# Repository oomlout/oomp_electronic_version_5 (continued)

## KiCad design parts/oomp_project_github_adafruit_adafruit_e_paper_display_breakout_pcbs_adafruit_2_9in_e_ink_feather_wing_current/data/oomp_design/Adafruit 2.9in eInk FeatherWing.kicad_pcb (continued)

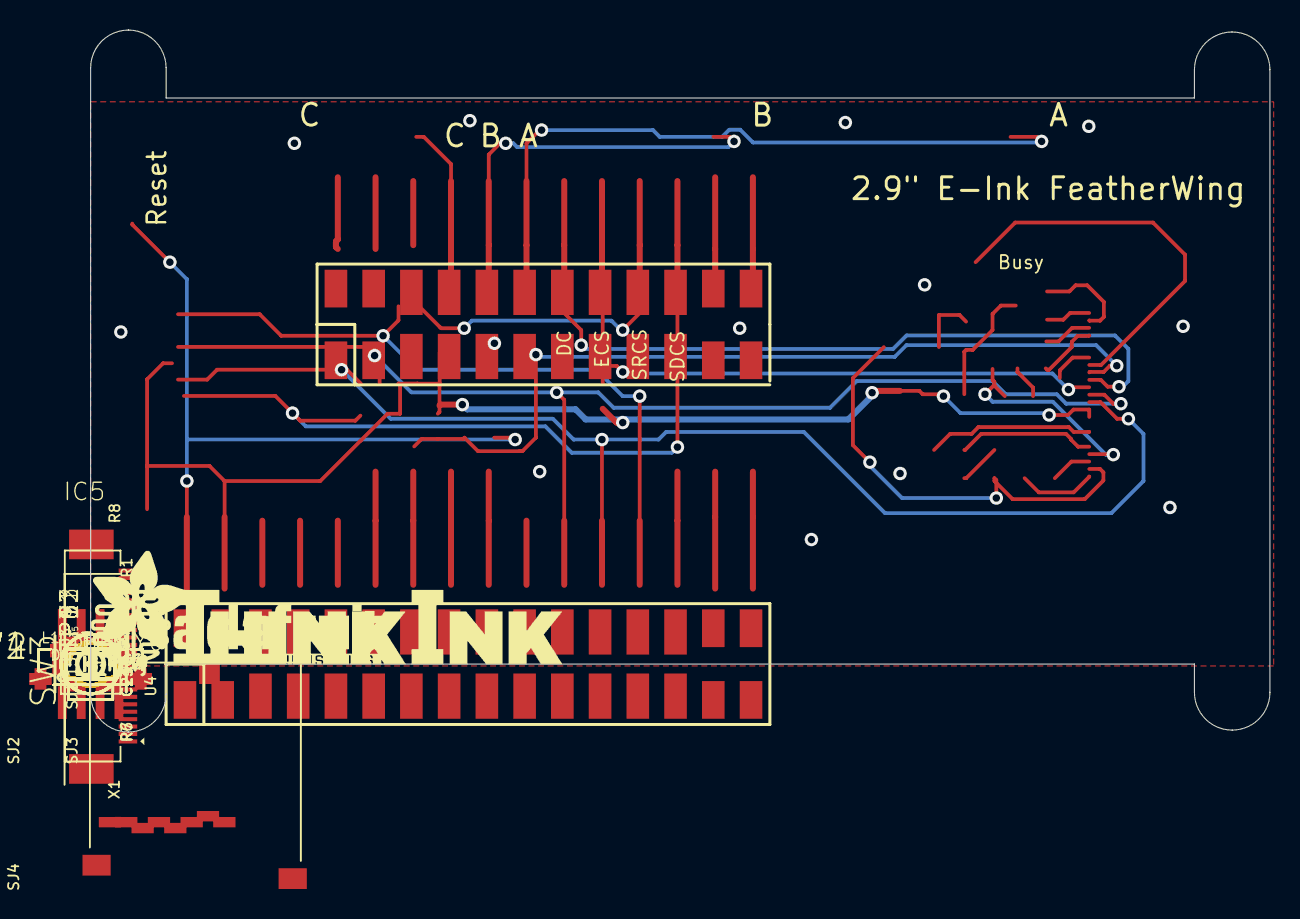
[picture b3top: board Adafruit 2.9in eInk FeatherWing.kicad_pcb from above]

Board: 2 copper layers, 79.4 x 47.2 mm, 59 parts (1 on the bottom side), 46 nets.

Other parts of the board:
U$8: THINKINK_1.25IN
U$9: PCBFEAT-REV-040
U$17: ADAFRUIT_TEXT_20MM

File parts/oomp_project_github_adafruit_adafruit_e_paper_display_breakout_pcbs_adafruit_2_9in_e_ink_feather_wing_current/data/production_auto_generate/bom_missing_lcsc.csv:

Designator,Comment,Footprint,OOMP ID,Reason
BUSY0,TPTP15SQ,Adafruit 2.9in eInk FeatherWing-import-fps:TP15SQ,,No verified LCSC part number
C1,1uF,Adafruit 2.9in eInk FeatherWing-import-fps:0805_10MGAP,,No verified LCSC part number
C2,1uF/10V,Adafruit 2.9in eInk FeatherWing-import-fps:0805-NO,,No verified LCSC part number
C3,1uF/25V,Adafruit 2.9in eInk FeatherWing-import-fps:0805-NO,,No verified LCSC part number
C4,1uF/25V,Adafruit 2.9in eInk FeatherWing-import-fps:0805-NO,,No verified LCSC part number
C5,10uF/25V,Adafruit 2.9in eInk FeatherWing-import-fps:0805-NO,electronic_capacitor_0805_10_micro_farad,No verified LCSC part number
C6,1uF/10V,Adafruit 2.9in eInk FeatherWing-import-fps:0805-NO,,No verified LCSC part number
C15,10uF/10V+,Adafruit 2.9in eInk FeatherWing-import-fps:0805-NO,electronic_capacitor_0805_10_micro_farad,No verified LCSC part number
C16,1uF,Adafruit 2.9in eInk FeatherWing-import-fps:0805-NO,,No verified LCSC part number
C21,10µF,Adafruit 2.9in eInk FeatherWing-import-fps:0805-NO,electronic_capacitor_0805_10_micro_farad,No verified LCSC part number
C22,1uF/25V,Adafruit 2.9in eInk FeatherWing-import-fps:0805-NO,,No verified LCSC part number
C23,1uF/25V,Adafruit 2.9in eInk FeatherWing-import-fps:0805-NO,,No verified LCSC part number
C24,1uF,Adafruit 2.9in eInk FeatherWing-import-fps:0805-NO,,No verified LCSC part number
D1,MBR0530,Adafruit 2.9in eInk FeatherWing-import-fps:SOD-123,,No verified LCSC part number
D2,MBR0530,Adafruit 2.9in eInk FeatherWing-import-fps:SOD-123,,No verified LCSC part number
D3,MBR0530,Adafruit 2.9in eInk FeatherWing-import-fps:SOD-123,,No verified LCSC part number
D4,1N4148,Adafruit 2.9in eInk FeatherWing-import-fps:SOD-323F,electronic_diode_switching_sod_323_onsemi_1n4148ws,No verified LCSC part number
EINK1,EINK_24PIN_290IN,Adafruit 2.9in eInk FeatherWing-import-fps:EINK_290IN,,No verified LCSC part number
IC5,AXP803,Adafruit 2.9in eInk FeatherWing-import-fps:SOT23,,No verified LCSC part number
L1,10uH,Adafruit 2.9in eInk FeatherWing-import-fps:INDUCTOR_4X4MM_NR401,,No verified LCSC part number
MS1,FEATHERWING_SMTDUALNOHOLES,Adafruit 2.9in eInk FeatherWing-import-fps:FEATHERWING_SMT_NOHOLES,,No verified LCSC part number
Q5,IRLML0100,Adafruit 2.9in eInk FeatherWing-import-fps:SOT23-3,,No verified LCSC part number
R4,.47ohm,Adafruit 2.9in eInk FeatherWing-import-fps:0805_10MGAP,,No verified LCSC part number
SW1,,Adafruit 2.9in eInk FeatherWing-import-fps:SPST_TACTILE_RA,,No verified LCSC part number
SW2,,Adafruit 2.9in eInk FeatherWing-import-fps:SPST_TACTILE_RA,,No verified LCSC part number
SW3,,Adafruit 2.9in eInk FeatherWing-import-fps:SPST_TACTILE_RA,,No verified LCSC part number
SW4,,Adafruit 2.9in eInk FeatherWing-import-fps:SPST_TACTILE_RA,,No verified LCSC part number
TP1,TPTP15SQ,Adafruit 2.9in eInk FeatherWing-import-fps:TP15SQ,,No verified LCSC part number
TP2,TPTP15SQ,Adafruit 2.9in eInk FeatherWing-import-fps:TP15SQ,,No verified LCSC part number
TP3,TPTP15SQ,Adafruit 2.9in eInk FeatherWing-import-fps:TP15SQ,,No verified LCSC part number
TP4,TPTP15SQ,Adafruit 2.9in eInk FeatherWing-import-fps:TP15SQ,,No verified LCSC part number
TP5,TPTP15SQ,Adafruit 2.9in eInk FeatherWing-import-fps:TP15SQ,,No verified LCSC part number
TP6,TPTP15SQ,Adafruit 2.9in eInk FeatherWing-import-fps:TP15SQ,,No verified LCSC part number
TP7,TPTP15SQ,Adafruit 2.9in eInk FeatherWing-import-fps:TP15SQ,,No verified LCSC part number
TP8,TPTP15SQ,Adafruit 2.9in eInk FeatherWing-import-fps:TP15SQ,,No verified LCSC part number
TP9,TPTP15SQ,Adafruit 2.9in eInk FeatherWing-import-fps:TP15SQ,,No verified LCSC part number
TP11,TPTP15SQ,Adafruit 2.9in eInk FeatherWing-import-fps:TP15SQ,,No verified LCSC part number
TP12,TPTP15SQ,Adafruit 2.9in eInk FeatherWing-import-fps:TP15SQ,,No verified LCSC part number
TP13,TPTP15SQ,Adafruit 2.9in eInk FeatherWing-import-fps:TP15SQ,,No verified LCSC part number
U4,23K256-I/SN,Adafruit 2.9in eInk FeatherWing-import-fps:SOIC8_150MIL,,No verified LCSC part number
U$8,,Adafruit 2.9in eInk FeatherWing-import-fps:THINKINK_1.25IN,,No verified LCSC part number
U$9,,Adafruit 2.9in eInk FeatherWing-import-fps:PCBFEAT-REV-040,,No verified LCSC part number
U$17,,Adafruit 2.9in eInk FeatherWing-import-fps:ADAFRUIT_TEXT_20MM,,No verified LCSC part number
X1,MICROSD,Adafruit 2.9in eInk FeatherWing-import-fps:MICROSD,,No verified LCSC part number

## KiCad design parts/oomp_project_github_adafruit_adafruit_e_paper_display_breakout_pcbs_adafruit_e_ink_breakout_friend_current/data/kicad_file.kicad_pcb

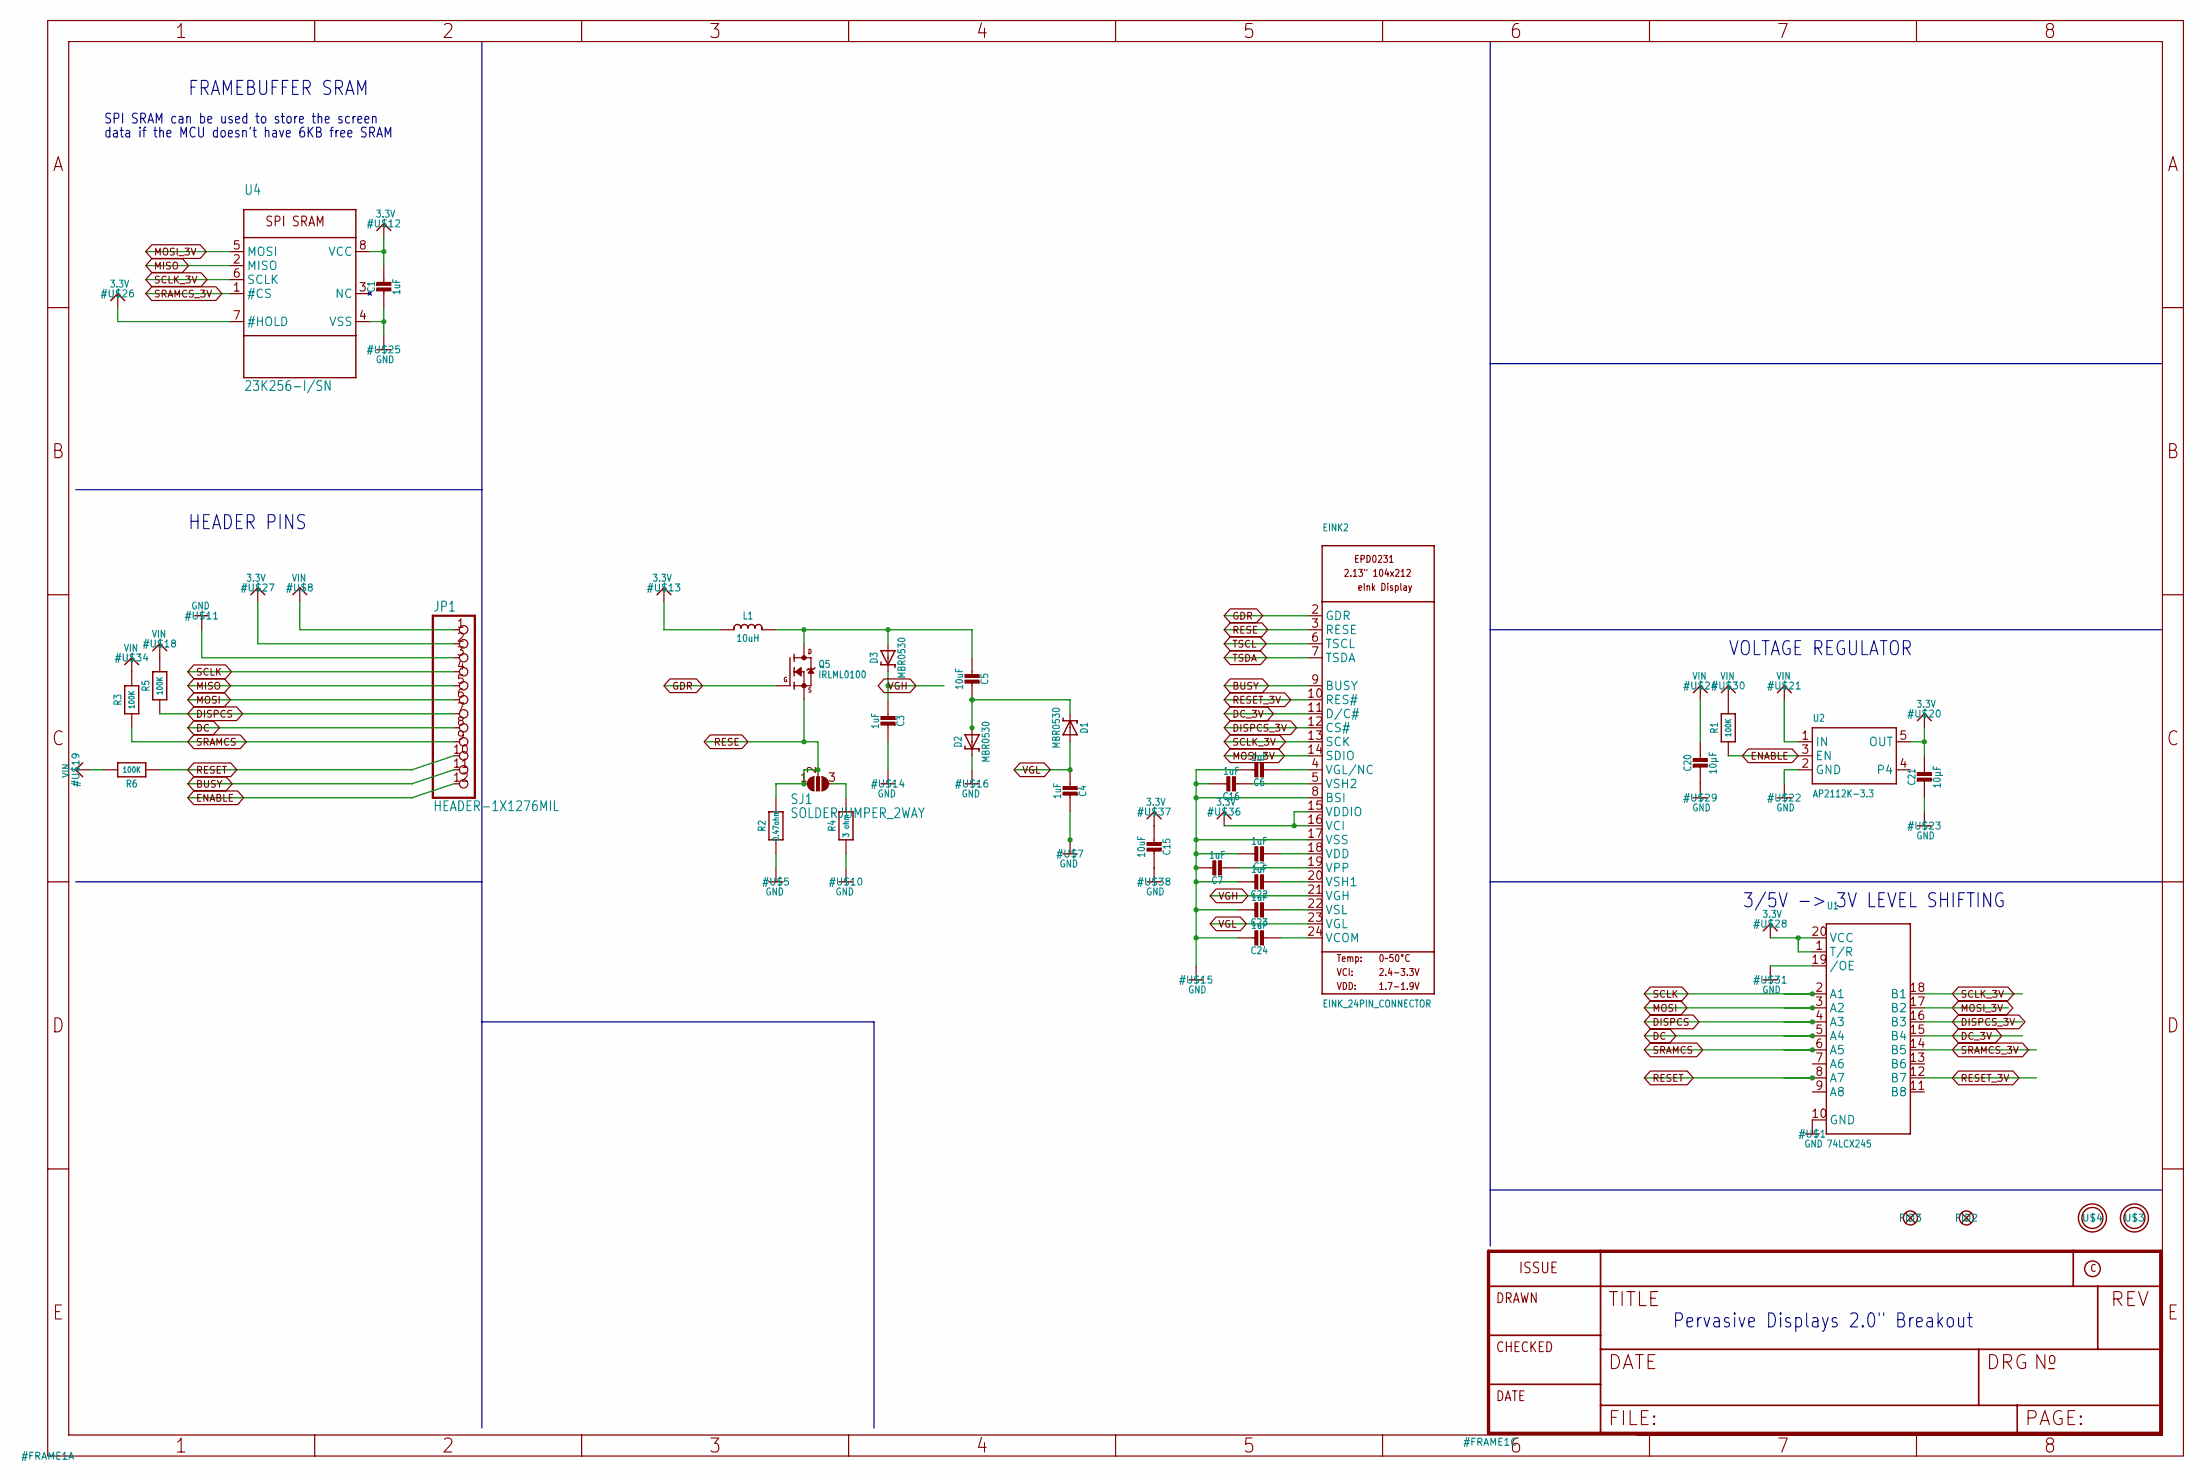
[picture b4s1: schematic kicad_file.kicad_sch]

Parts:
C1: 1uF; 0805_10MGAP
C2, C3, C4, C6, C7, C16, C22, C23, C24: 1uF; 0805-NO
C5, C15: 10uF; 0805-NO
C20, C21: 10µF; 0805-NO
D1, D2, D3: MBR0530; SOD-123
EINK2: EINK_24PIN_CONNECTOR; EINK_24PIN
FID2, FID3: FIDUCIAL_1MM
JP1: HEADER-1X1276MIL; 1X12_ROUND_76MIL
L1: 10uH; INDUCTOR_4X4MM_NR401
Q5: IRLML0100; SOT23-3
R1, R3, R5, R6: 100K; 0603-NO
R2: 0.47ohm; 0805-NO
R4: 3 ohm; 0805-NO
SJ1: SOLDERJUMPER_2WAY; SOLDERJUMPER_2WAY_OPEN_NOPASTE
U1: 74LCX245; TSSOP20
U2: AP2112K-3.3; SOT23-5
U4: 23K256-I/SN; SOIC8_150MIL
U$3, U$4: MOUNTINGHOLE2.5; MOUNTINGHOLE_2.5_PLATED

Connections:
3.3V: C1.1, C15.2, C21.1, EINK2.15 (VDDIO), EINK2.16 (VCI), JP1.2, L1.P$2 (2), U1.1 (T/R), U1.20 (VCC), U2.5 (OUT), U4.7 (#HOLD), U4.8 (VCC)
BUSY: EINK2.9 (BUSY), JP1.11
DC: JP1.8, U1.5 (A4)
DC_3V: EINK2.11 (D/C#), U1.15 (B4)
DISPCS: JP1.7, R5.1, U1.4 (A3)
DISPCS_3V: EINK2.12 (CS#), U1.16 (B3)
ENABLE: JP1.12, R1.1, U2.3 (EN)
GDR: EINK2.2 (GDR), Q5.1 (G)
GND: C1.2, C2.1, C3.2, C4.2, C6.1, C7.1, C15.1, C16.1, C20.2, C21.2, C22.1, C23.1, C24.1, D2.C, EINK2.8 (BSI), EINK2.17 (VSS), JP1.3, R2.2, R4.2, U1.10 (GND), U1.19 (/OE), U2.2 (GND), U4.4 (VSS)
MISO: JP1.5, U4.2 (MISO)
MOSI: JP1.6, U1.3 (A2)
MOSI_3V: EINK2.14 (SDIO), U1.17 (B2), U4.5 (MOSI)
unnamed: C7.2, EINK2.19 (VPP)
unnamed: C5.2, D1.C, D2.A
unnamed: C5.1, D3.A, L1.P$1 (1), Q5.3 (D)
unnamed: C16.2, EINK2.5 (VSH2)
unnamed: C2.2, EINK2.18 (VDD)
unnamed: C22.2, EINK2.20 (VSH1)
unnamed: R4.1, SJ1.3
unnamed: C6.2, EINK2.4 (VGL/NC)
unnamed: C23.2, EINK2.22 (VSL)
unnamed: C24.2, EINK2.24 (VCOM)
RESE: EINK2.3 (RESE), Q5.2 (S), R2.1, SJ1.1, SJ1.2
RESET: JP1.10, R6.1, U1.8 (A7)
RESET_3V: EINK2.10 (RES#), U1.12 (B7)
SCLK: JP1.4, U1.2 (A1)
SCLK_3V: EINK2.13 (SCK), U1.18 (B1), U4.6 (SCLK)
SRAMCS: JP1.9, R3.1, U1.6 (A5)
SRAMCS_3V: U1.14 (B5), U4.1 (#CS)
TSCL: EINK2.6 (TSCL)
TSDA: EINK2.7 (TSDA)
VGH: C3.1, D3.C, EINK2.21 (VGH)
VGL: C4.1, D1.A, EINK2.23 (VGL)
VIN: C20.1, JP1.1, R1.2, R3.2, R5.2, R6.2, U2.1 (IN)

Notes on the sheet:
SPI SRAM can be used to store the screen
FRAMEBUFFER SRAM
VOLTAGE REGULATOR
3/5V -> 3V LEVEL SHIFTING
Pervasive Displays 2.0" Breakout
HEADER PINS
data if the MCU doesn't have 6KB free SRAM

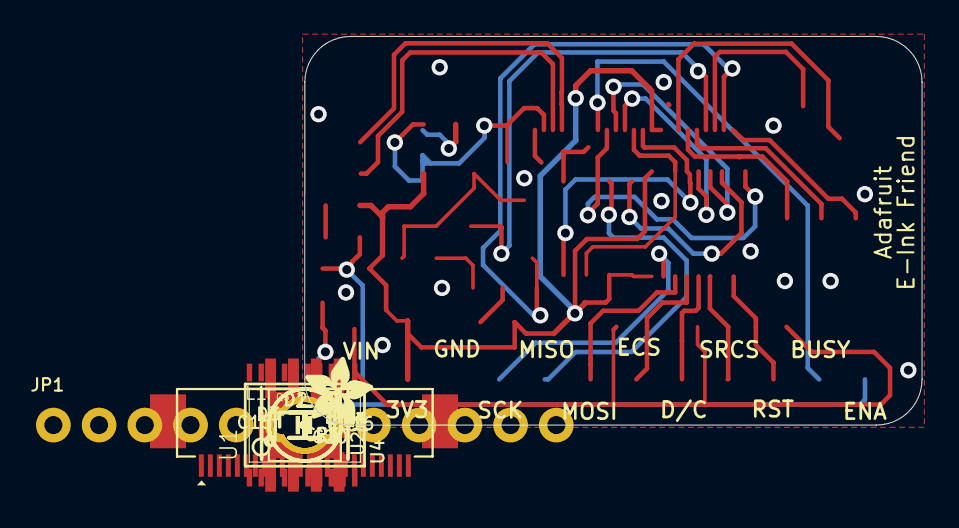
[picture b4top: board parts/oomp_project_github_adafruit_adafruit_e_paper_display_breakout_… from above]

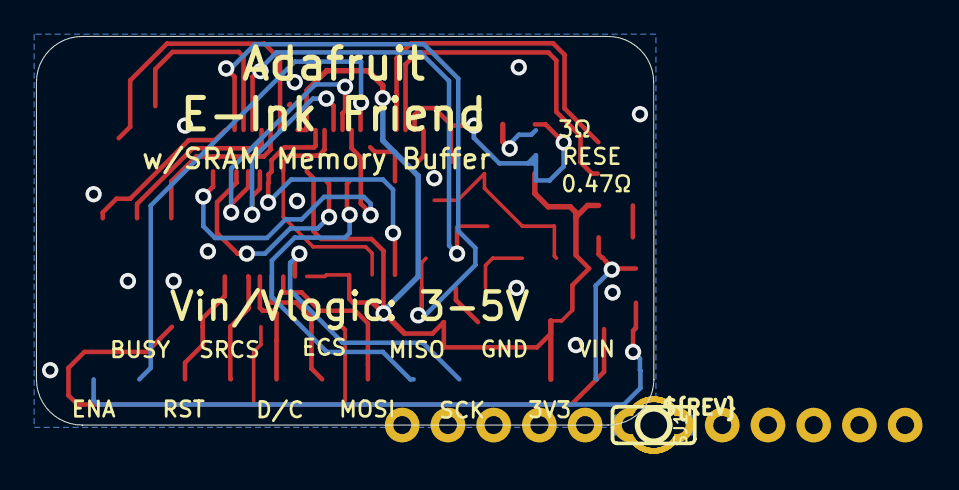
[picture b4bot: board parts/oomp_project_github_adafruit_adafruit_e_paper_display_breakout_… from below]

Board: 2 copper layers, 34.3 x 21.6 mm, 37 parts (2 on the bottom side), 32 nets.

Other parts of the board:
U$2: ADAFRUIT_3.5MM
U$9: PCBFEAT-REV-040

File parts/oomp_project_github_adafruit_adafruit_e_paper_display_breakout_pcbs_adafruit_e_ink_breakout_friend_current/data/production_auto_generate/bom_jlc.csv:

Comment,Designator,Footprint,LCSC Part #
,JP1,Adafruit eInk Breakout Friend-import-fps:1X12_ROUND_76MIL,C7501588
,U$2,Adafruit eInk Breakout Friend-import-fps:ADAFRUIT_3.5MM,
,U$9,Adafruit eInk Breakout Friend-import-fps:PCBFEAT-REV-040,
,U1,Adafruit eInk Breakout Friend-import-fps:TSSOP20,
0.47ohm,R2,Adafruit eInk Breakout Friend-import-fps:0805-NO,
100K,"R1,R3,R5,R6",Adafruit eInk Breakout Friend-import-fps:0603-NO,C25803
10uF,"C5,C15",Adafruit eInk Breakout Friend-import-fps:0805-NO,
10uH,L1,Adafruit eInk Breakout Friend-import-fps:INDUCTOR_4X4MM_NR401,
10µF,"C20,C21",Adafruit eInk Breakout Friend-import-fps:0805-NO,
1uF,"C2,C3,C4,C6,C7,C16,C22,C23,C24",Adafruit eInk Breakout Friend-import-fps:0805-NO,
1uF,C1,Adafruit eInk Breakout Friend-import-fps:0805_10MGAP,
23K256-I/SN,U4,Adafruit eInk Breakout Friend-import-fps:SOIC8_150MIL,
3 ohm,R4,Adafruit eInk Breakout Friend-import-fps:0805-NO,
AP2112K-3.3,U2,Adafruit eInk Breakout Friend-import-fps:SOT23-5,
EINK_24PIN_CONNECTOR,EINK2,Adafruit eInk Breakout Friend-import-fps:EINK_24PIN,
IRLML0100,Q5,Adafruit eInk Breakout Friend-import-fps:SOT23-3,
MBR0530,"D1,D2,D3",Adafruit eInk Breakout Friend-import-fps:SOD-123,

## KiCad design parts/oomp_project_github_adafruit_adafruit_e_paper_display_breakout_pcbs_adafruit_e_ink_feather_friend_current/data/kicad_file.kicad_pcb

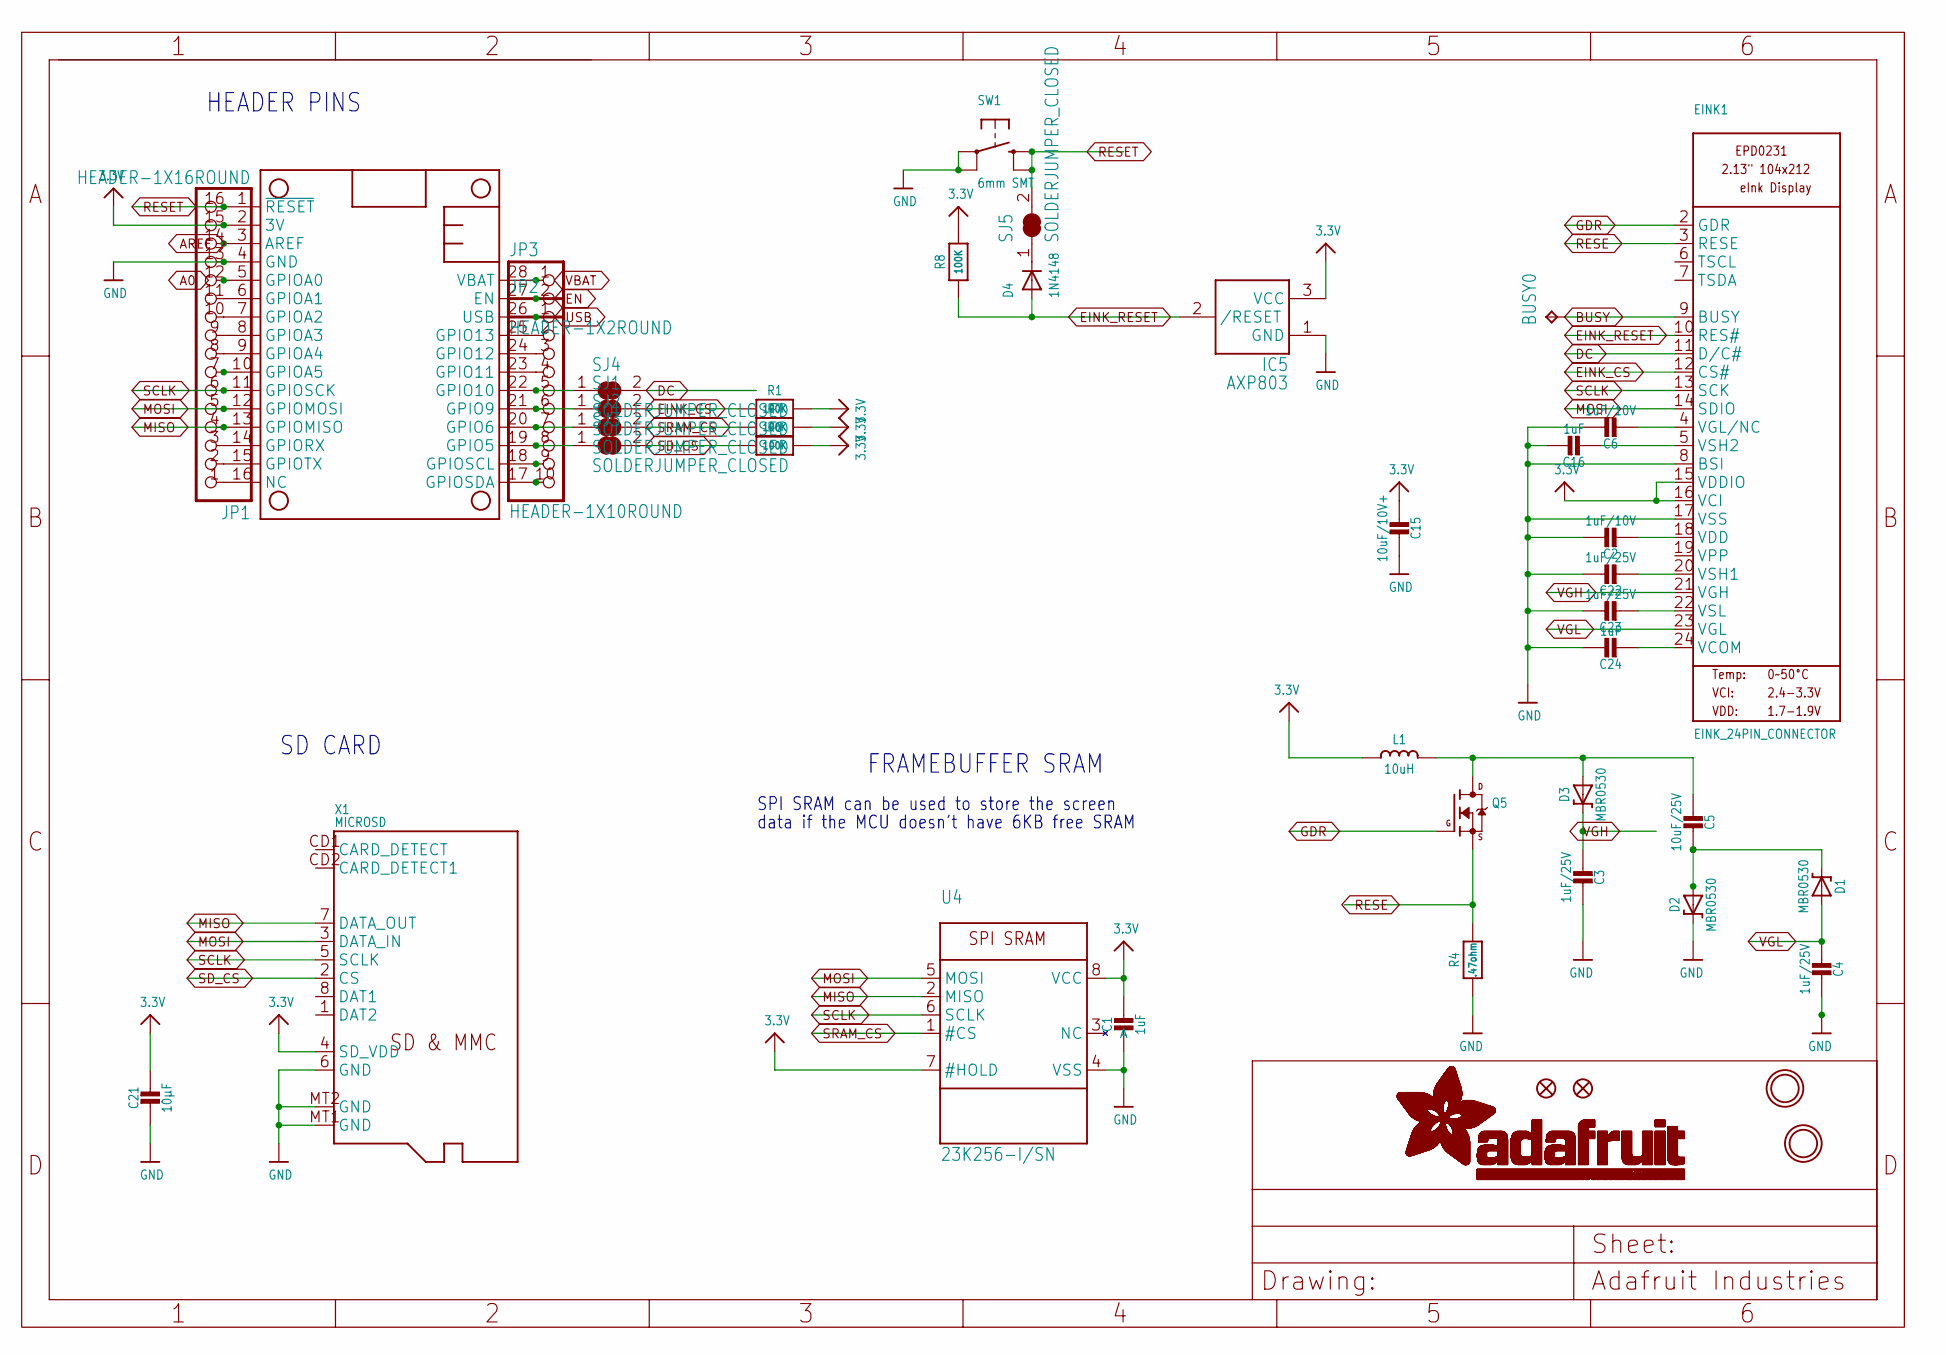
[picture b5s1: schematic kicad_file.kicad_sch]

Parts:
BUSY0: TPTP15SQ; TP15SQ
C1: 1uF; 0805_10MGAP
C2, C6: 1uF/10V; 0805-NO
C3, C4, C22, C23: 1uF/25V; 0805-NO
C5: 10uF/25V; 0805-NO
C15: 10uF/10V+; 0805-NO
C16, C24: 1uF; 0805-NO
C21: 10µF; 0805-NO
D1, D2, D3: MBR0530; SOD-123
D4: 1N4148; SOD-323F
EINK1: EINK_24PIN_CONNECTOR; EINK_24PIN
FID1, FID3: FIDUCIAL_1MM
IC5: AXP803; SOT23
JP1: HEADER-1X16ROUND; 1X16_ROUND
JP2: HEADER-1X10ROUND; 1X10_ROUND
JP3: HEADER-1X2ROUND; 1X02_ROUND
L1: 10uH; INDUCTOR_4X4MM_NR401
MS1: FEATHERWING_NOHOLES
Q5: IRLML0100; SOT23-3
R1, R6, R7, R8: 100K; 0603-NO
R4: .47ohm; 0805_10MGAP
SJ1, SJ2, SJ3, SJ4, SJ5: SOLDERJUMPER_CLOSED; SOLDERJUMPER_CLOSEDWIRE
SW1: 6mm SMT; BTN_KMR2_4.6X2.8
U4: 23K256-I/SN; SOIC8_150MIL
U$3, U$4: MOUNTINGHOLE2.5; MOUNTINGHOLE_2.5_PLATED
X1: MICROSD

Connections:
3.3V: C1.1, C15.2, C21.1, EINK1.15 (VDDIO), EINK1.16 (VCI), IC5.3 (VCC), JP1.15, L1.P$2 (2), MS1.2 (3V), R1.2, R6.2, R7.2, R8.2, U4.7 (#HOLD), U4.8 (VCC), X1.4 (SD_VDD)
A0: JP1.12, MS1.5 (GPIOA0)
AREF: JP1.14, MS1.3 (AREF)
BUSY: BUSY0.TP, EINK1.9 (BUSY)
DC: EINK1.11 (D/C#), SJ4.2
EINK_CS: EINK1.12 (CS#), R1.1, SJ1.2
EINK_RESET: D4.A, EINK1.10 (RES#), IC5.2 (/RESET), R8.1
EN: JP3.2, MS1.27 (EN)
GDR: EINK1.2 (GDR), Q5.1 (G)
GND: C1.2, C2.1, C3.2, C4.2, C6.1, C15.1, C16.1, C21.2, C22.1, C23.1, C24.1, D2.C, EINK1.8 (BSI), EINK1.17 (VSS), IC5.1 (GND), JP1.13, MS1.4 (GND), R4.2, SW1.A, SW1.A' (P1), U4.4 (VSS), X1.6 (GND), X1.MT1 (GND), X1.MT2 (GND)
H: JP2.8, MS1.19 (GPIO5), SJ3.1
I: JP2.7, MS1.20 (GPIO6), SJ2.1
J: JP2.6, MS1.21 (GPIO9), SJ1.1
K: JP2.5, MS1.22 (GPIO10), SJ4.1
MISO: JP1.4, MS1.13 (GPIOMISO), U4.2 (MISO), X1.7 (DATA_OUT)
MOSI: EINK1.14 (SDIO), JP1.5, MS1.12 (GPIOMOSI), U4.5 (MOSI), X1.3 (DATA_IN)
unnamed: JP1.7, MS1.10 (GPIOA5)
unnamed: C5.2, D1.C, D2.A
unnamed: C5.1, D3.A, L1.P$1 (1), Q5.3 (D)
unnamed: C16.2, EINK1.5 (VSH2)
unnamed: C2.2, EINK1.18 (VDD)
unnamed: C22.2, EINK1.20 (VSH1)
unnamed: D4.C, SJ5.1
unnamed: JP1.11, MS1.6 (GPIOA1)
unnamed: C6.2, EINK1.4 (VGL/NC)
unnamed: JP1.10, MS1.7 (GPIOA2)
unnamed: JP1.9, MS1.8 (GPIOA3)
unnamed: JP1.8, MS1.9 (GPIOA4)
unnamed: JP1.3, MS1.14 (GPIORX)
unnamed: JP1.2, MS1.15 (GPIOTX)
unnamed: JP1.1, MS1.16 (NC)
unnamed: JP2.10, MS1.17 (GPIOSDA)
unnamed: JP2.9, MS1.18 (GPIOSCL)
unnamed: JP2.4, MS1.23 (GPIO11)
unnamed: JP2.3, MS1.24 (GPIO12)
unnamed: JP2.2, MS1.25 (GPIO13)
unnamed: C23.2, EINK1.22 (VSL)
unnamed: C24.2, EINK1.24 (VCOM)
RESE: EINK1.3 (RESE), Q5.2 (S), R4.1
RESET: JP1.16, MS1.1 (~RESET), SJ5.2, SW1.B (S), SW1.B' (S1)
SCLK: EINK1.13 (SCK), JP1.6, MS1.11 (GPIOSCK), U4.6 (SCLK), X1.5 (SCLK)
SD_CS: R6.1, SJ3.2, X1.2 (CS)
SRAM_CS: R7.1, SJ2.2, U4.1 (#CS)
USB: JP2.1, MS1.26 (USB)
VBAT: JP3.1, MS1.28 (VBAT)
VGH: C3.1, D3.C, EINK1.21 (VGH)
VGL: C4.1, D1.A, EINK1.23 (VGL)

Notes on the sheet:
FRAMEBUFFER SRAM
SPI SRAM can be used to store the screen
data if the MCU doesn't have 6KB free SRAM
HEADER PINS
SD CARD

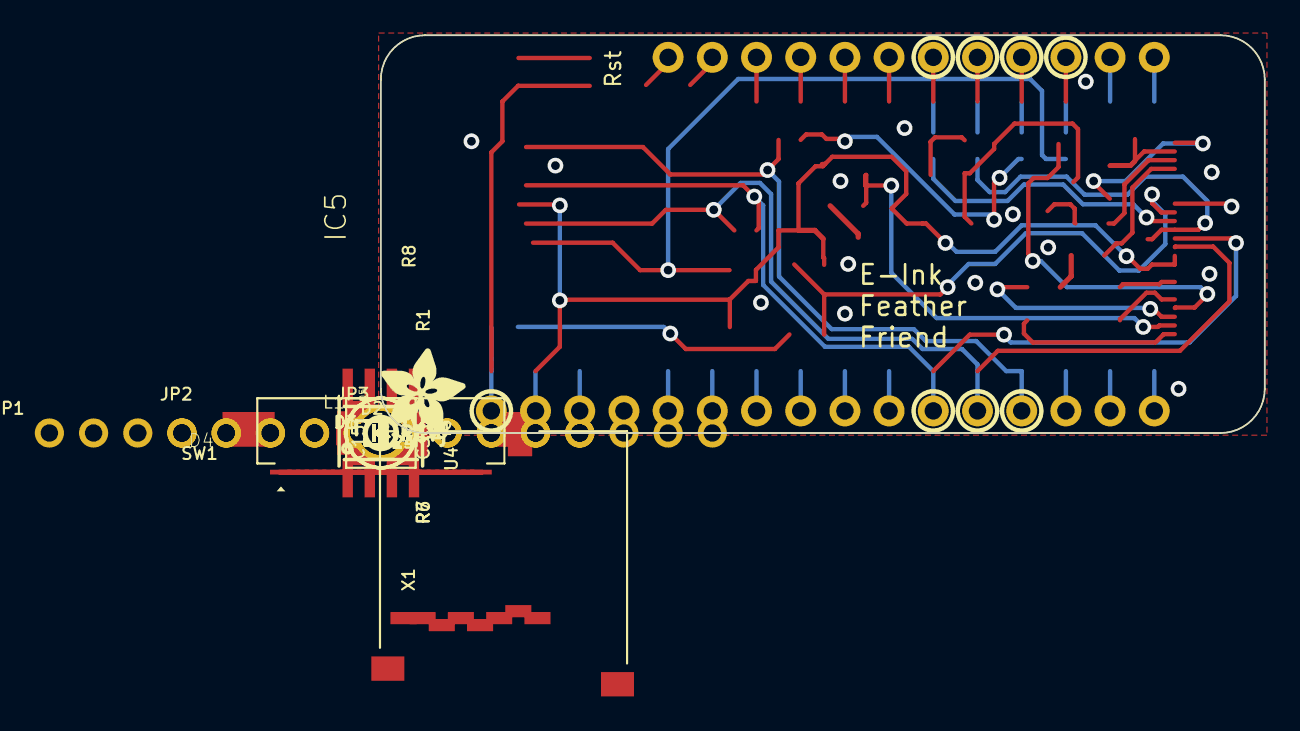
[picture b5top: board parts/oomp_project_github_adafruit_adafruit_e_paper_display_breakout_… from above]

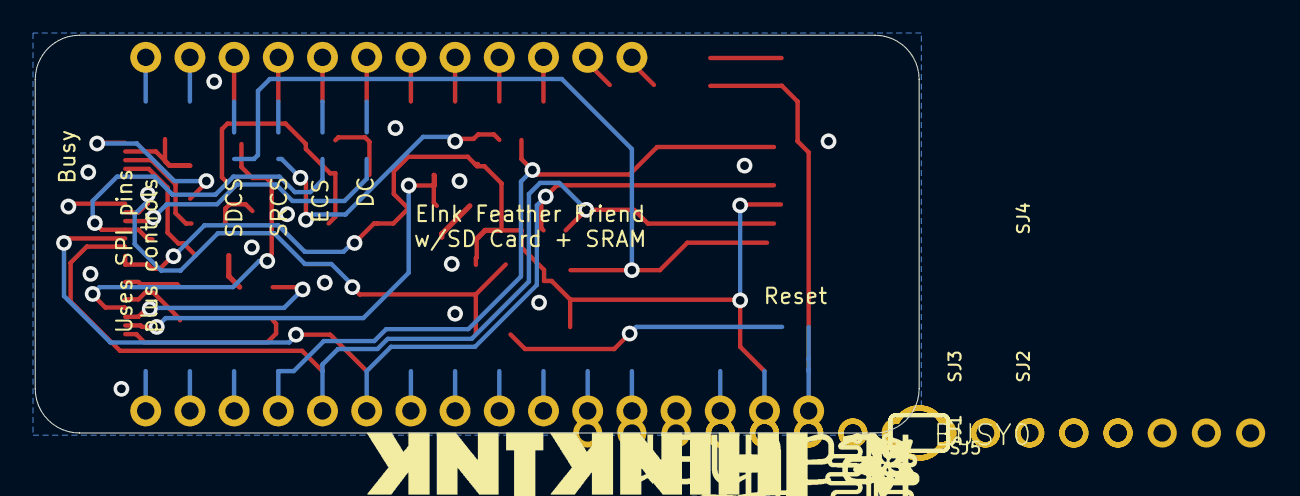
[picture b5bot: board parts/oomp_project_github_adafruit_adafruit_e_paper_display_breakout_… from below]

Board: 2 copper layers, 50.8 x 22.9 mm, 47 parts (9 on the bottom side), 47 nets.

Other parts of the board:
U$5: THINKINK_1.25IN
U$6: FEATHERLOGO_MED
U$8: ADAFRUIT_5MM
U$9: PCBFEAT-REV-040
U$17: ADAFRUIT_3.5MM

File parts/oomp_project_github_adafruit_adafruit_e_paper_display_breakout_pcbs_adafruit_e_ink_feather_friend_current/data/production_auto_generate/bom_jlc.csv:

Comment,Designator,Footprint,LCSC Part #
,JP3,Adafruit eInk Feather Friend-import-fps:1X02_ROUND,C492401
,JP2,Adafruit eInk Feather Friend-import-fps:1X10_ROUND,C57369
,JP1,Adafruit eInk Feather Friend-import-fps:1X16_ROUND,C7501270
,U$17,Adafruit eInk Feather Friend-import-fps:ADAFRUIT_3.5MM,
,U$8,Adafruit eInk Feather Friend-import-fps:ADAFRUIT_5MM,
,U$6,Adafruit eInk Feather Friend-import-fps:FEATHERLOGO_MED,
,U$9,Adafruit eInk Feather Friend-import-fps:PCBFEAT-REV-040,
,U$5,Adafruit eInk Feather Friend-import-fps:THINKINK_1.25IN,
.47ohm,R4,Adafruit eInk Feather Friend-import-fps:0805_10MGAP,
100K,"R1,R6,R7,R8",Adafruit eInk Feather Friend-import-fps:0603-NO,C25803
10uF/10V+,C15,Adafruit eInk Feather Friend-import-fps:0805-NO,
10uF/25V,C5,Adafruit eInk Feather Friend-import-fps:0805-NO,
10uH,L1,Adafruit eInk Feather Friend-import-fps:INDUCTOR_4X4MM_NR401,
10µF,C21,Adafruit eInk Feather Friend-import-fps:0805-NO,
1N4148,D4,Adafruit eInk Feather Friend-import-fps:SOD-323F,
1uF,"C16,C24",Adafruit eInk Feather Friend-import-fps:0805-NO,
1uF,C1,Adafruit eInk Feather Friend-import-fps:0805_10MGAP,
1uF/10V,"C2,C6",Adafruit eInk Feather Friend-import-fps:0805-NO,
1uF/25V,"C3,C4,C22,C23",Adafruit eInk Feather Friend-import-fps:0805-NO,
23K256-I/SN,U4,Adafruit eInk Feather Friend-import-fps:SOIC8_150MIL,
6mm SMT,SW1,Adafruit eInk Feather Friend-import-fps:BTN_KMR2_4.6X2.8,
AXP803,IC5,Adafruit eInk Feather Friend-import-fps:SOT23,
EINK_24PIN_CONNECTOR,EINK1,Adafruit eInk Feather Friend-import-fps:EINK_24PIN,
FEATHERWING_NOHOLES,MS1,Adafruit eInk Feather Friend-import-fps:FEATHERWING_NOHOLES,
IRLML0100,Q5,Adafruit eInk Feather Friend-import-fps:SOT23-3,
MBR0530,"D1,D2,D3",Adafruit eInk Feather Friend-import-fps:SOD-123,
MICROSD,X1,Adafruit eInk Feather Friend-import-fps:MICROSD,
TPTP15SQ,BUSY0,Adafruit eInk Feather Friend-import-fps:TP15SQ,
